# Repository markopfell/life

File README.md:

Fortune favors the brave.

<!-- Pliny The Younger -->

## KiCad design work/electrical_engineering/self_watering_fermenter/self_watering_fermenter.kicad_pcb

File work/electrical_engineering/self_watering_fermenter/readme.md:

readme.md
    the readme you are reading

self_watering_fermenter.drawio
    Roughly diagrams the structural, and non electronic connections to the other parts of the system

(self_watering_fermenter_diagram.drawio.svg.png)

.kicad_sch
   self watering circuit schematic

RPI_PICO-20231005-v1.21.0.uf2
    For flashing micropython on a raspberry pi pico
main.py
    necessary file name micropython uses to run upon boot and is the self watering fermenter code

Theory of operation is described:  https://docs.google.com/document/d/1Th5y-gPPo2V6W9uRYwj1-cUWkCRWNlDgZwDqT0uh-yE/edit?tab=t.0
Pictures TBD

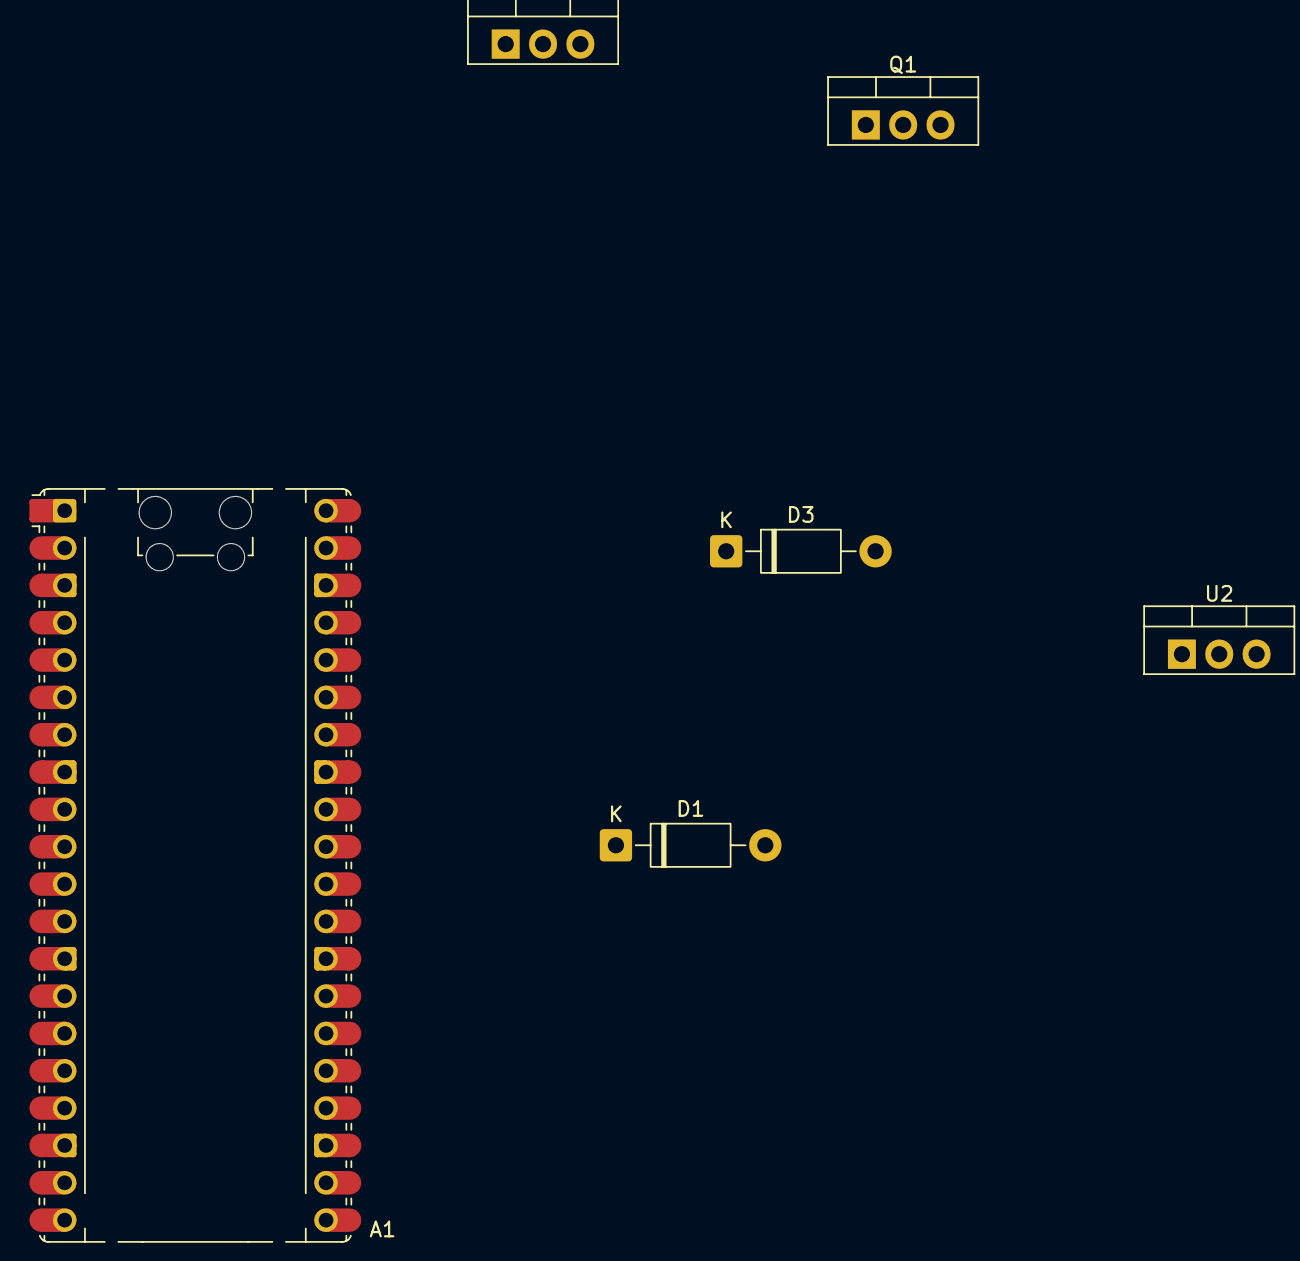
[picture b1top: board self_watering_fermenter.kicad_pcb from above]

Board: 2 copper layers, 6 parts (0 on the bottom side), 4 nets, no tracks yet.

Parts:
A1: RaspberryPi_Pico; RaspberryPi_Pico_Common_Unspecified
D1, D3: 1N4004; D_DO-41_SOD81_P10.16mm_Horizontal
Q1: IRLB8721PBF; TO-220-3_Vertical
U1, U2: LM317_TO-220; TO-220-3_Vertical

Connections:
+5V: D3.2 (A), U1.2 (VO)
GND: A1.39 (VSYS), Q1.3 (S)
unnamed: D1.1 (K), U1.3 (VI), U2.3 (VI)
unnamed: D3.1 (K), Q1.2 (D)

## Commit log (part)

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2018-12-11 Read filenames from files in a folder
2018-12-11 actual title of moon and actual representative raws
2018-12-11 Renamed from moon->daphnis
2018-12-11 github linguist test experiment
2018-12-11 reverted github linguist experiement?
2018-12-11 Functon, constant, and variabling ...
2018-12-11 Reversed unreversable changes
2018-12-11 90 degree rotation to align this middle image with the first image in the tryptch
2018-12-13 Removed github? junk
2018-12-18 Removed badly named output file
2018-12-18 Google job posting io skeleton
2018-12-18 Simple natural language tool kit library up and running
2018-12-18 Dropped an extension
2018-12-18 Initializing
2018-12-18 A little clean-up featuring nltk examples
2018-12-28 Splat and Zip; Unpacking and repacking of argument lists
2019-01-29 Zip and splat operator
2019-01-29 Kymeta year 1 and cleanup
2019-01-30 Appended RF-ness to job titles
2019-01-30 associate and after role detail expansion
2019-01-30 associate role actual text
2019-01-30 newline drop
2019-01-30 Broke up blocks of text for readability
2019-01-30 Tightned up wording of Senior RF SSL position to fit on page 1
2019-02-06 Generalized to Exposure and Skills
2019-07-29 Tweaks to exposure/skills and added in Leostella work
2019-08-18 Salary comments
2019-10-02 Tweaked wording
2019-10-06 Added more Kymeta job experience and tweaked some word and skills
2019-10-24 Staging for rf communications utility functions
2019-10-24 EIRP and G/T functions
2019-11-17 Clean up commit
2019-11-20 Folded job post kwargs into resume anyway and some minor wording nits on standards and RF kwargs
2019-11-20 Update resume names for efficiency
2019-12-23 Missed .pdf
2020-01-05 Link budget skeleton
2020-01-05 Filled in path loss free space function
2020-01-05 Filled in ebn0
2020-01-09 Saturn and rings view
2020-01-14 Added link budget key word and updated Ski Mountaineering to the more accurate Splitboard Mountaineering
2020-01-19 Updated kwargs to better match postings
2020-01-30 Initial commit of splitboard mountaineering routes
2020-02-17 DVB-S2 NOT DVBS-2
2020-03-24 Folder clean up
2020-04-28 Kwarg stuffing for Kymeta position
2020-05-30 Raw makes more sense as a name
2020-06-05 Basic sweepable link budget with visual output
2020-06-10 NASA and general stoplight margins: go, slow down, and stop
2020-06-15 Staging for parameterization
2020-06-15 Rough altitude parameterization function
2020-06-16 Fixed calculation error and vectorized ionosphere and troposphere losses
2020-06-16 Vectorized path_loss_free_space
2020-06-17 Broke out link margin vs beamwidth calculation functions and plotting routine
2020-06-17 Replaced math library with numpy for all due to better array handling
2020-06-30 Reworked hands-on testing section for rf pcb and exposure/skills
2020-07-29 Python kwarg stuffing and word wrangling
2020-08-04 Actual measured correction factor for n modled secondary antenna gains
2020-09-12 Present tense on the open source stuff
2020-10-12 Forgot to commit human readable output
2020-10-22 Metal print from photo lab upscales nicely
2020-12-08 More specific wording in exposure/skills and job title
2020-12-10 Highlighting more software work than hardware work
2021-05-28 Cleaned up significant a/descents
2021-06-15 Tweaked mountaineering portion of resume to fit 2 pages
2021-06-15 Since DVB-S2 standard is in Es/N0 it's nice to have a conversion to pure bits
2021-06-15 Added DVB-S2 modcod vs Es/N0 from final pdf of standard
2021-06-16 DVB-S2 modcod reader
2021-06-22 DVB-S2 modcod searcher
2021-06-22 dvbs2 stuff looks up correct esn0, spectral efficiency, and back calculates minimum ebn0 and coding gain for link calculation
2021-07-06 Broken code, fix by redoing linspace calls after generating primary and secondary antenna beamwidth model
2021-07-08 Re-ordering, polishing, and fleshing out Leostella work
2021-07-08 Re-ordering, polishing, and fleshing out Leostella work ++
2021-07-13 Minor wording tweaks
2021-07-28 GPS is more specific than L-band
2021-08-10 Resume binning started for non-engineering work
2021-09-07 first cut of mountain guide resume
2021-09-13 Turns out you can electrical engineer and mountain guide simultanesously so folder cleanup necessary for verb-ing
2021-09-13 Regenerated pdf for show and tell
2021-09-13 Removed top roped only routes as movement into sport->trad climbs
2021-09-14 .gitignore now wokring
2021-09-14 .gitignore now working
2021-10-06 Adding certifications for apprentice alpine guide application
2021-10-13 Removed ice climbing since not really much of a thing and edited rock climbing to show specific disciple and grade
2021-10-20 Changed leostella work to past tense
2021-11-01 Icicle creek exploration
2021-11-01 Added Albedo work placeholder
2021-11-05 Shuffled and cleaned things around for an AnyMission pandas ingestion
2021-11-05 Shuffled and cleaned things around for an AnyMission pandas ingestion again
2021-11-06 Albedo micro blurb
2021-11-06 Tweak Albedo wording
2021-11-18 SDR and cloud kwarg stuffing
2021-11-18 Cloud providers per public knowledge
2021-11-21 Tweaked Albedo work tagline
2021-12-09 Updated for digitized RF, satellite networks, and general cloud kwargs
2021-12-09 Ephasized high level strategy and end-to-end architecture decisions
2021-12-11 Minor phrasing
2021-12-11 Breaking up the huge Leostella text block
2021-12-24 Better Albedo wording
2022-01-30 Reorganized Exposure and Skills plus added multiple of same design working in spaaaace
2022-01-30 Added primarily Helens #2
2022-03-10 Added a tour and removed one that I did literally no touring on, aka granite = never put on skins
2022-03-22 Leostella polishing
2022-03-27 Another sport climb
2022-03-31 Tweaked exposure and skills to remove VBA coding ... really don't want to do that ever again
2022-03-31 Volcano
2022-05-03 spelling
2022-05-08 Swaped easy cascades and smith stuff for vantage rock climbing diversity
2022-05-19 communicate more with less
2022-05-21 years of experience somewhat eye roll
2022-06-22 Exposure and skills section polishing
2022-06-24 GNU radio finally after all these years
2022-06-27 Exposure and skills prioritization, tweaking, and work experience kwarg stuffing
2022-07-05 Kwarg stuffing
2022-07-10 Wording tweaking
2022-08-15 Tooling around with CCSDS:
2022-08-15 Skills verbage tweak
2022-08-24 OSI layer kwarg stuffing
2022-08-25 First trad lead yay
2022-08-25 Tweaking formatting for single pitch instructor
2022-09-22 Notes
2022-10-05 Cleaned up trad subsection and added multipitch subsection
2022-10-13 Not committing certificaiton pdfs since no reason to track changes, but added link to them
2022-11-08 Broke up a run on sentance
2022-11-10 Prioritization
2022-12-11 Minor tweaking
2022-12-19 Removed education because why is that necessary
2022-12-22 Re-tweak
2023-01-18 Comment only
2023-02-05 Added another bc splitboard tour and a tweak
2023-02-05 Wording tweak for actual code production
2023-02-05 Digital focus to Albedo work
2023-02-25 Uncommented out resume stuff for more kwargs
2023-02-27 East peak tour bb
2023-04-25 All 10+ climbs are now trad and or multipitch
2023-06-17 Completed Alpine Skills course and tweaked certification section
2023-07-27 More climbs
2023-07-27 Multi pitch greater than single pitch
2023-08-05 activity description tweaks
2023-08-16 streamline visual sectinos of certs
2023-08-16 capitalization
2023-09-18 Minor tweaking to the actionable verbs the last 9 months turned into
2023-09-21 Clean up top level section to move from skills to certs
2023-09-21 Initial commit of mountain guide cover letter
2023-09-22 Schedule kwarg stuffing
2023-09-22 Passed washington food handling permit
2023-09-23 removed extraneous file
2023-10-04 Glaciated differentiation
2023-10-06 beefed up Albedo stuff
2023-10-09 Word smithing
2023-10-09 Zig zag
2023-10-12 ee works lolz
2023-10-12 Clean up client vs guide on Helens, Baker, Rainier
2023-11-02 Yosemite trip Late october 2023
2023-11-02 initial commit of cookbook
2023-11-03 Verbage tweak
2023-11-04 Formattting tweak
2023-11-12 Spacing lineup
2023-11-20 Ingrediants to the right
2023-11-20 Minor essay on compression. Go with ingrediants up front
2023-12-05 intial code
2023-12-09 before cleanup
2023-12-10 final hopefully
2023-12-17 debugging
2023-12-17 ingrediants up front as that is how I shop
2023-12-23 Even more Notes
2024-02-18 Avalanche Recreation Level 2 and minor spacing
2024-03-11 Albedo tweak
2024-03-26 A bunch of multipitch in Cochise Stronghold
2024-04-01 Cochise Stronghold
2024-04-01 Only brief intro to VITA49 removed
2024-04-13 First cut of working with c and or c++ code for real time megahertz rate digital signal processing
2024-05-15 Finally bashed my way to linear feedback shift register polynomial pseudo random number generation
2024-07-01 Amazon
2024-07-01 Squamish Grade IIIs
2024-07-01 tried reversing taps
2024-07-01 c library test python wrapper
2024-07-05 Albedo past tense
2024-09-21 Squamish
2024-10-19 more tweaks
2024-10-20 final tweaks
2024-11-10 tweaked regulatory section
2024-11-10 regenerated
2024-12-03 Cisco networking technician exam passed
2024-12-09 grammer fix
2024-12-10 networking front and central
2025-01-22 two recipies
2025-01-22 created recipies folder for easier version control and distribution
2025-01-23 minor tweak
2025-01-23 90 percent typeset
2025-02-18 5th overnight backcountry ski trip pushed off the page electrical engineering work ... which is fine
2025-02-18 Amazon in there
2025-03-21 ignore source files
2025-03-21 Painted a more detailed picture of my regulatory work
2025-03-21 Highlighted satellite constellations though this might not be the best strategy for this line of work
2025-03-21 Initial commit of first freelancer mathematical python project
2025-03-28 moved and clean up
2025-03-28 Bringing it back
2025-03-28 More keywords
2025-03-31 Link capacity and hardware testing detailing
2025-06-21 spruced up bedo
2025-07-06 hardware in the loop x2 is better than flatsat
2025-07-10 More cover letters
2025-07-17 Initial commit of pcb files
2025-07-17 first cut of schematic
2025-07-17 First cut of readme for various files in repository
2025-07-18 added custom symbol for the liquid level sensor
2025-07-18 First cut of potential pcb
2025-07-27 Soldered and working
2025-08-14 Relish route is actually sport whoops
2025-08-27 more junk folders ignored
2025-08-27 initial commit to find one way aka quiet streets in long beach
2025-08-28 working find of zillow html of head tag
2025-08-29 mixed diagram
2025-08-29 weird drawio backups ignored
2025-08-29 added bill of materials
2025-08-29 rough bom committed
2025-08-30 simplified block diagram for using power mosfet
2025-08-30 Major note for actual power transistor and appropriately sized regulators of 1 A current
2025-09-01 find address works but just grabs the first address
2025-09-01 multiple addresses from zillow now yay
2025-09-01 extracted contents of address tag
2025-09-01 Base descriptor
2025-09-01 format tweak
2025-09-01 framed up final functions with return values
2025-09-01 Added cardinal directions
2025-09-02 Easy google search query cmd plus left click on link works
2025-09-03 Linting
2025-09-03 Wording tweak
2025-09-06 making room for other cities
2025-09-06 logic for multiple cities
2025-09-06 renaming refactoring overwrote specific key in open street maps query now fixed
2025-09-06 slightly wider search criteria for acceptable cities close to work
2025-09-11 link equations
2025-09-11 test
2025-09-11 test 2
2025-09-21 Error vector magnitude equation
2025-09-29 python binary byte and boolean arrays with numpy
2025-09-29 cleaned up junk
2025-09-29 Error vector magnitude equation as it is important for SNR
2025-10-09 maybe keep bar cart, donate china junk armed thing planter, and move bikes
2025-10-09 108 gaviota
2025-10-14 moved to seperate folders for different programming languages
2025-11-15 Added certifications and swapped FPGA for Cloud skills and exposure mostly
2026-01-17 minor cleanup
2026-01-29 made volcano ascents more specific
2026-02-04 mmore land
2026-02-23 More FPGA stuff at RS
2026-05-13 Tweaks for TTC focus
